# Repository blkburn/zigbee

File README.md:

# Zigbee

This repository contains multiple projects relating to teh Zigbee wireless protocol.

- zed_sensor_cc2652
- hardware
- sensor controller
- zigbee2mqtt

---

## zed_sensor_cc2652

This is a Zigbee End Device based on the Texas Instruments CC2652R1. It supports the following sensors (with build switches):
- AHT10 Temperature and Humidity Sensor
- APDS9930 Digital Proximity and Ambient Light Sensor
- LTR390 UV Light Sensor
- PIR Movement Sensor
- Reed Switch (Door opening sensor)
- Mains Energy Monitor (split coil current transformer)

The Sensor Controller handles all the sensor communications, while the main process handles the Zigbee stack and a custom task to process sensor reading and notify the Zigbee stack.

Tested with Zigbee2MQTT version 1.22.1 commit: 89996835

Master branch is currently built with:
* CCStudio version: 11.1.0.00011 
* SDK: simplelink_cc13x2_26x2_sdk_5_20_00_52

update of https://github.com/blkburn/cc2652_zigbee_zed

---

## Hardware

KiCad schematic and PCB designs. Both boards have be manufactured, tested, and working.

### Zigbee End Device
Based on the CC2652R module from RF Star (RF-BM-2652B1).
This is version 2 of the Zigbee End Device design in https://github.com/blkburn/cc2652_zigbee_zed/tree/master/hardware/cc2652_rf_star, and supports all the sensors described above. The version 1 board working unmodified with the zed_sensor_cc2652 software.

### Zigbee Coordinator
Based on the CC2652P module from RF Star (RF-BM-2652P2). It is a daughter board for the Orange Pi Zero 2 (http://www.orangepi.org/Orange%20Pi%20Zero2/). The Orange Pi uses an Allwinner H616 processor and comfortably runs Ubuntu or Debian Linux (plus much cheaper than a Raspberry Pi 4).

---

## Sensor Controller

This contains all the sensor controller projects that are used in the Zigbee End Device.

## Zigbee2MQTT

This directory contains the custom javascript device file for zigbee2mqtt to recognize the sensors.

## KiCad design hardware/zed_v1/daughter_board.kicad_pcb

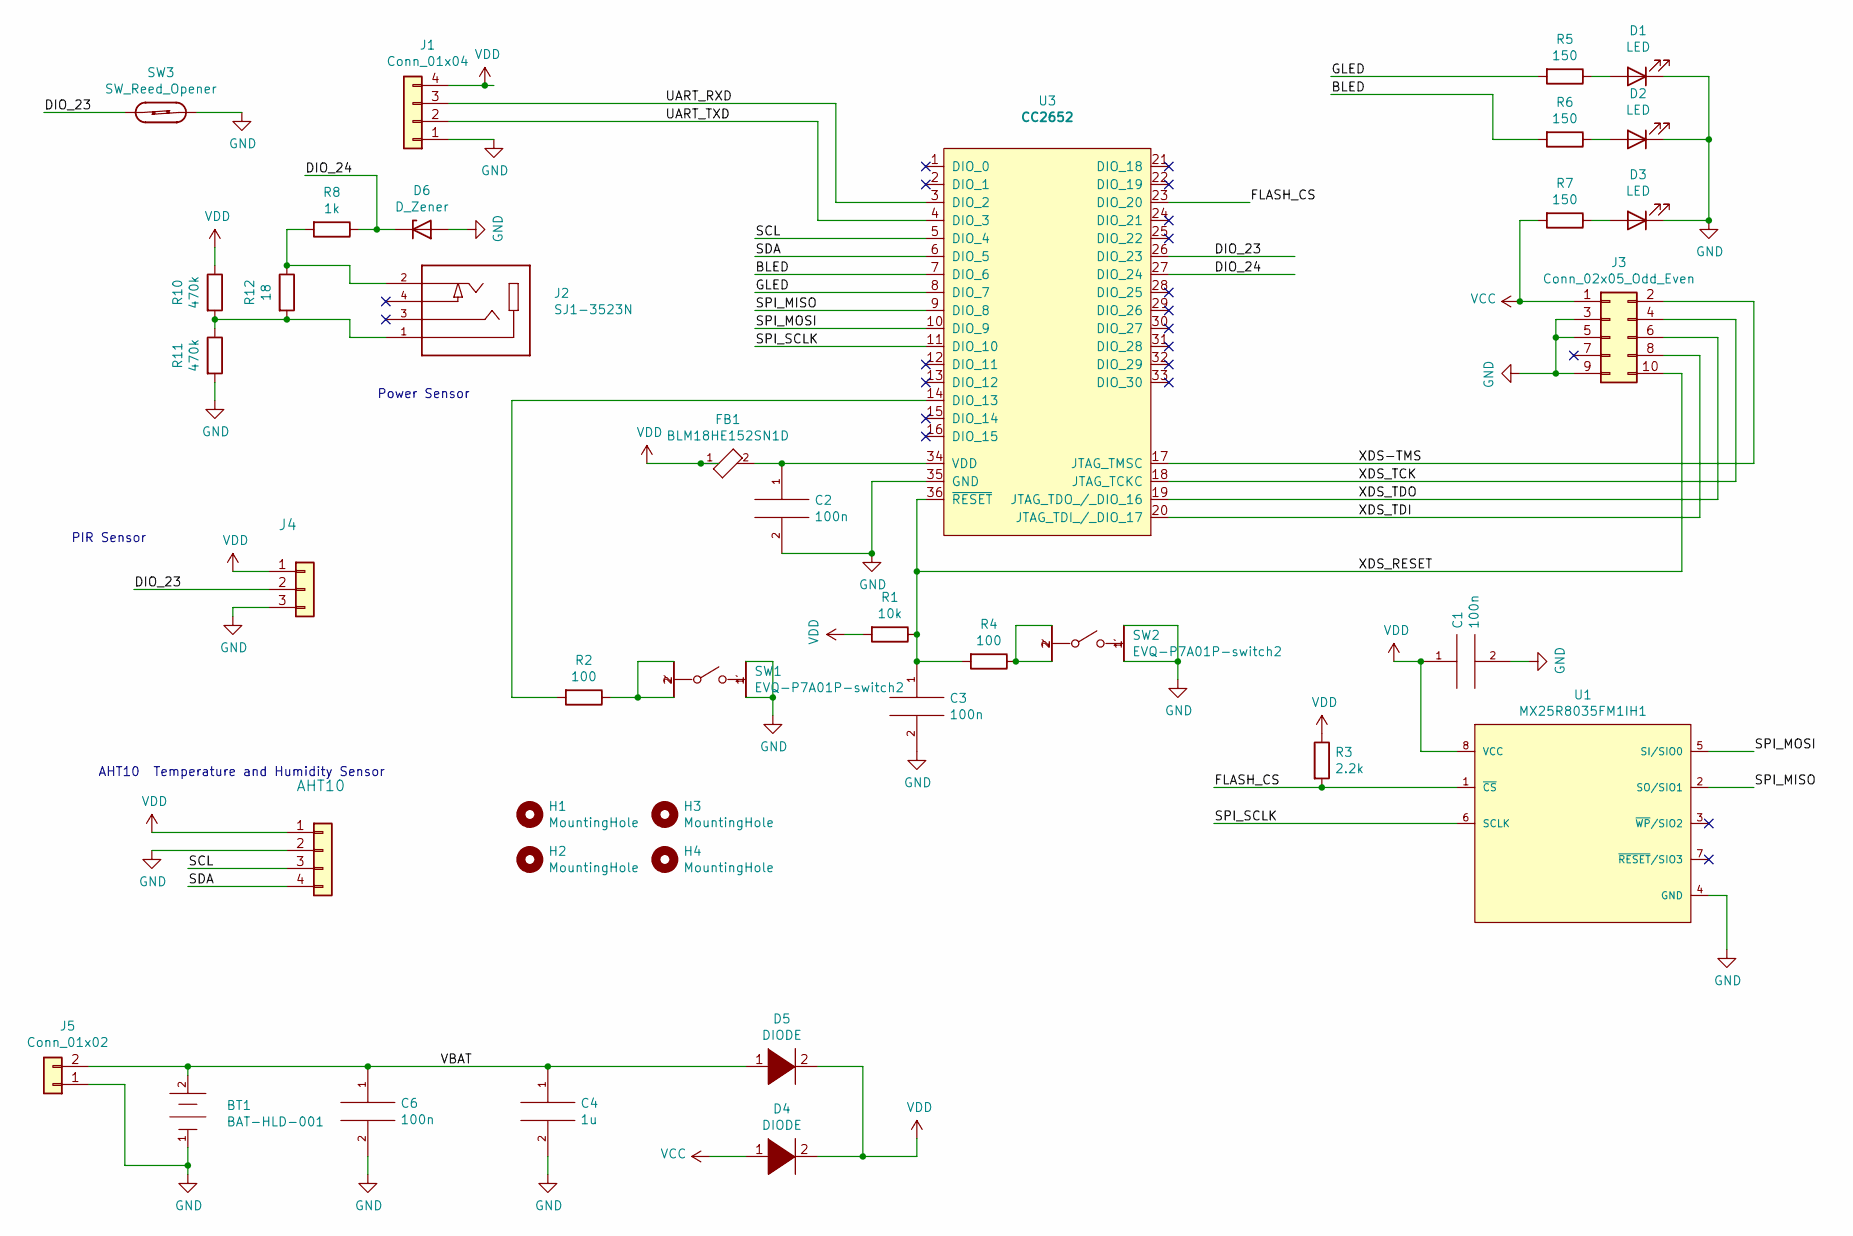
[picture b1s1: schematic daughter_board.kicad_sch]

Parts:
AHT10: Conn_01x04; PinHeader_1x04_P2.54mm_Vertical
BT1: BAT-HLD-001; Linx-BAT-HLD-001-0; mouser part number 712-BAT-HLD-001; digikey description HOLDER BATTERY 20MM COIN
C1, C2, C3, C6: 100n; C_0805_2012Metric
C4: 1u; C_0805_2012Metric
D1, D2, D3: LED; Lite-On-LTST-S220KRKT-0-0-0
D4, D5: DIODE; SOD-123FL
D6: D_Zener; D_SOD-923
FB1: BLM18HE152SN1D; R_0603_1608Metric_Pad0.98x0.95mm_HandSolder; tolerance 25%
H1, H2, H3, H4: MountingHole; MountingHole_2.7mm_M2.5_DIN965_Pad
J1: Conn_01x04; PinHeader_1x04_P2.54mm_Vertical
J2: SJ1-3523N; CUI_SJ-3524-SMT; PARTREV 1.02
J3: Conn_02x05_Odd_Even; PinHeader_2x05_P1.27mm_Vertical
J4: Conn_01x03; PinHeader_1x03_P2.54mm_Vertical
J5: Conn_01x02; JST_PH_B2B-PH-K_1x02_P2.00mm_Vertical
R1: 10k; R_0805_2012Metric
R2, R4: 100; R_0805_2012Metric
R3: 2.2k; R_0805_2012Metric
R5, R6, R7: 150; R_0805_2012Metric
R8: 1k; R_0805_2012Metric
R10, R11: 470k; R_0805_2012Metric
R12: 18; RESC1633X60N
SW1, SW2: EVQ-P7A01P-switch2; Panasonic-EVQ-P7A01P-0-0-MFG; voltage rating DC 12V; mouser part number 667-EVQP7A01P; digikey description SWITCH TACTILE SPST-NO 0.05A 12V
SW3: SW_Reed_Opener; R_Axial_DIN0309_L9.0mm_D3.2mm_P20.32mm_Horizontal
U1: MX25R8035FM1IH1; SOP-8_3.9x4.9mm_P1.27mm; digikey description IC FLASH 8M SPI 33MHZ 8USON
U3: CC2652; rf_star_cc2652

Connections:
/BLED: R6.2, U3.7 (DIO_6)
/DIO_23: J4.2, SW3.1, U3.26 (DIO_23)
/DIO_24: D6.1 (K), R8.1, U3.27 (DIO_24)
/FLASH_CS: R3.2, U1.1 (~CS), U3.23 (DIO_20)
/GLED: R5.2, U3.8 (DIO_7)
/SCL: AHT10.3, U3.5 (DIO_4)
/SDA: AHT10.4, U3.6 (DIO_5)
/SPI_MISO: U1.2 (SO/SIO1), U3.9 (DIO_8)
/SPI_MOSI: U1.5 (SI/SIO0), U3.10 (DIO_9)
/SPI_SCLK: U1.6 (SCLK), U3.11 (DIO_10)
/UART_RXD: J1.3, U3.3 (DIO_2)
/UART_TXD: J1.2, U3.4 (DIO_3)
/VBAT: BT1.2 (ANODE), C4.1, C6.1, D5.1 (K), J5.2
/XDS-TMS: J3.2, U3.17 (JTAG_TMSC)
/XDS_RESET: C3.1, J3.10, R1.1, R4.2, U3.36 (~RESET)
/XDS_TCK: J3.4, U3.18 (JTAG_TCKC)
/XDS_TDI: J3.8, U3.20 (JTAG_TDI_/_DIO_17)
/XDS_TDO: J3.6, U3.19 (JTAG_TDO_/_DIO_16)
GND: AHT10.2, BT1.1 (CATHODE), C1.2, C2.2, C3.2, C4.2, C6.2, D1.1 (K), D2.1 (K), D3.1 (K), D6.2 (A), J1.1, J3.3, J3.5, J3.9, J4.3, J5.1, R11.2, SW1.1, SW1.1', SW2.1, SW2.1', SW3.2, U1.4 (GND), U3.35 (GND)
unnamed: C2.1, FB1.2, U3.34 (VDD)
unnamed: D1.2 (A), R5.1
unnamed: D2.2 (A), R6.1
unnamed: D3.2 (A), R7.1
unnamed: J2.1, R10.2, R11.1, R12.2
unnamed: J2.2, R8.2, R12.1
unnamed: R2.1, SW1.2, SW1.2'
unnamed: R2.2, U3.14 (DIO_13)
unnamed: R4.1, SW2.2, SW2.2'
VCC: D4.1 (K), J3.1, R7.2
VDD: AHT10.1, C1.1, D4.2 (A), D5.2 (A), FB1.1, J1.4, J4.1, R1.2, R3.1, R10.1, U1.8 (VCC)

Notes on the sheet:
PIR Sensor
AHT10 Temperature and Humidity Sensor
Power Sensor

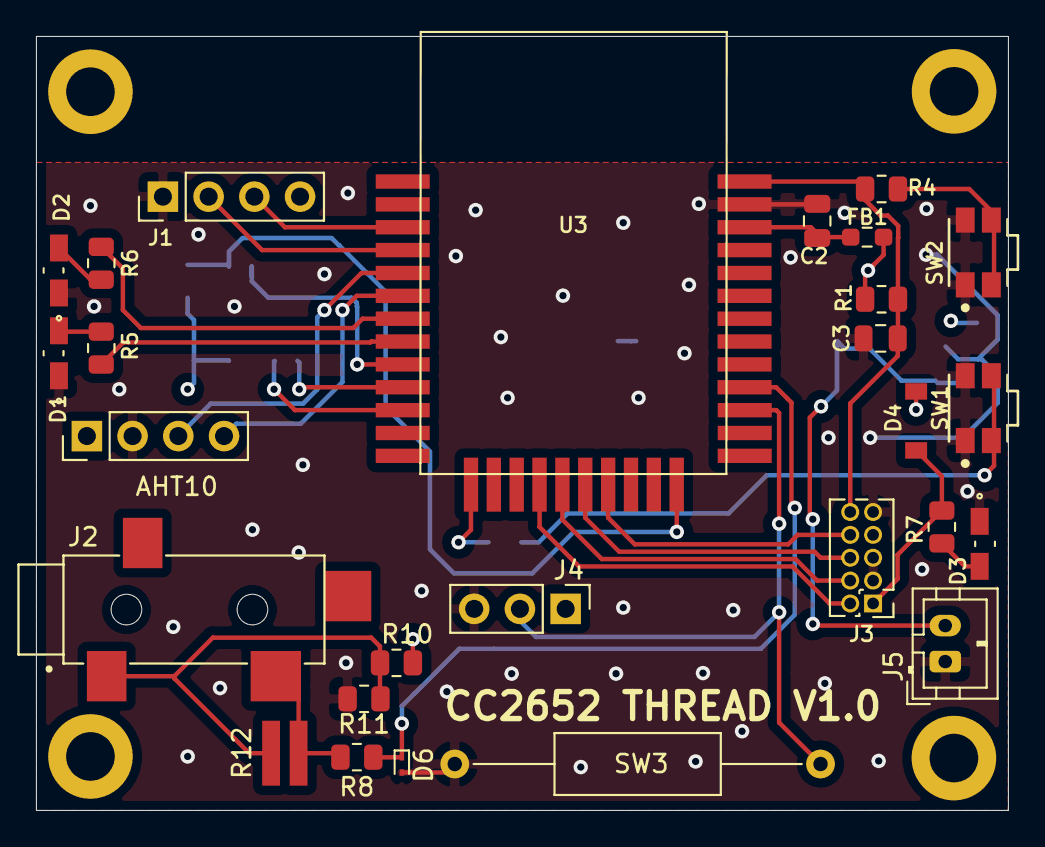
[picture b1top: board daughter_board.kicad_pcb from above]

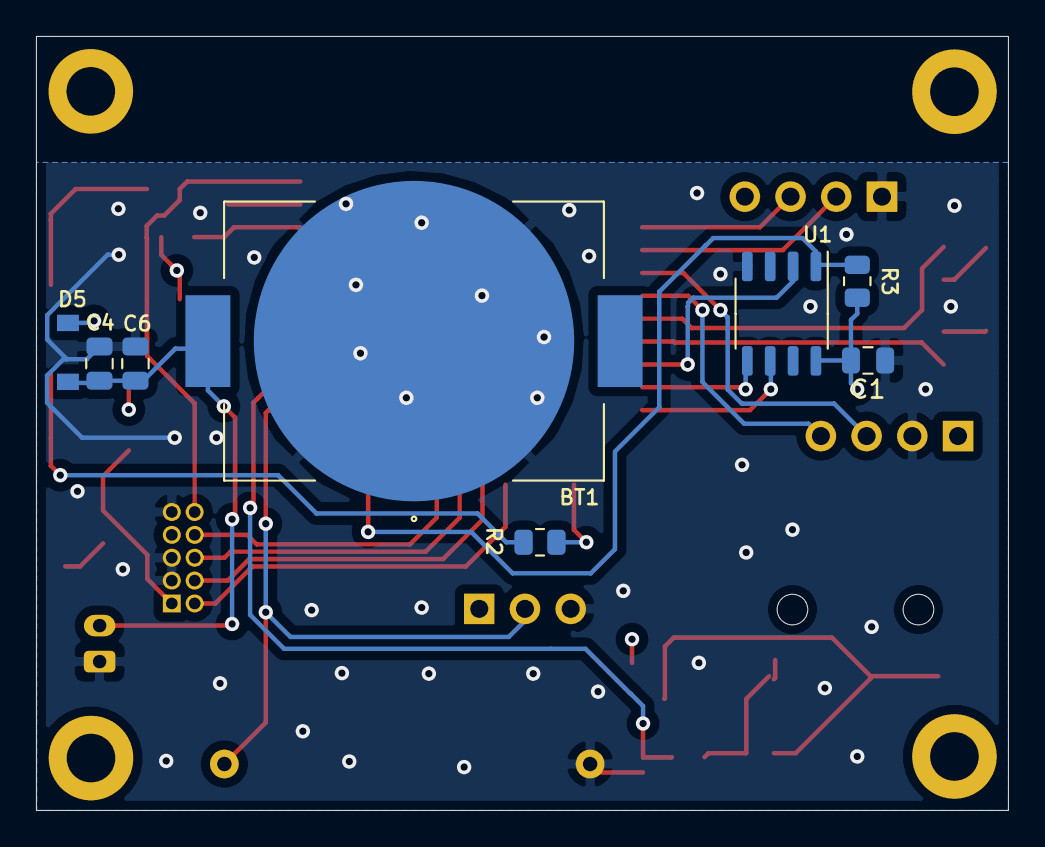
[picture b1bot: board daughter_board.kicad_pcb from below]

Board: 4 copper layers, 54.0 x 43.0 mm, 39 parts (8 on the bottom side), 30 nets.

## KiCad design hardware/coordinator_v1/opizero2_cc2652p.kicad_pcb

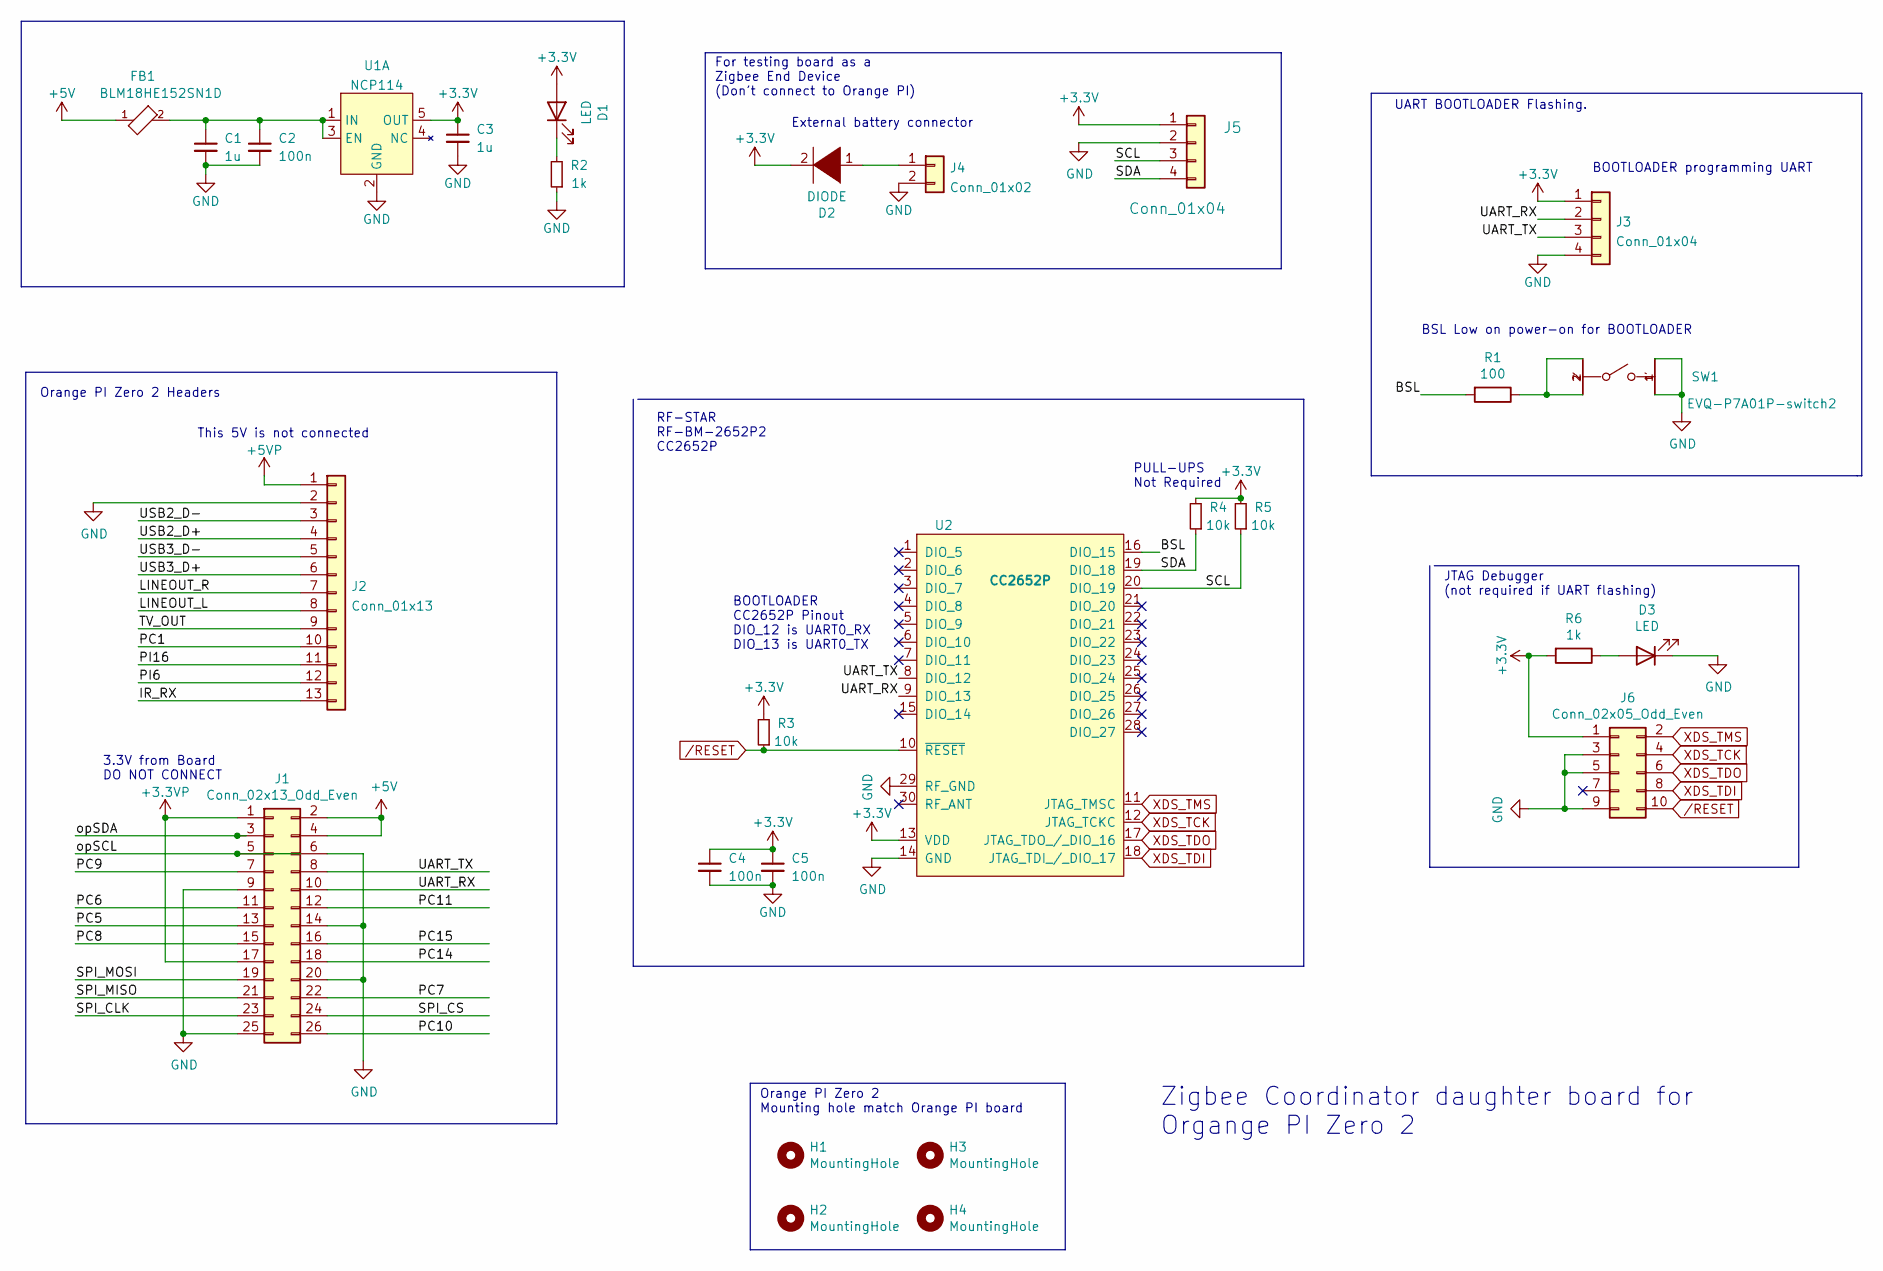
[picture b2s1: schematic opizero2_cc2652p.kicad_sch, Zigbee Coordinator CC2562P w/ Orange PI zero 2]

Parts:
C1, C3: 1u; C_1206_3216Metric; LCSC Part # C13585
C2, C4, C5: 100n; C_0805_2012Metric; LCSC Part # C13585
D1, D3: LED; Lite-On-LTST-S220KRKT-0-0-0
D2: DIODE; SOD-123FL
FB1: BLM18HE152SN1D; R_0603_1608Metric_Pad0.98x0.95mm_HandSolder; tolerance 25%
H1, H2, H3, H4: MountingHole; MountingHole_2.7mm_M2.5_ISO14580_Pad
J1: Conn_02x13_Odd_Even; PinHeader_2x13_P2.54mm_Vertical
J2: Conn_01x13; PinHeader_1x13_P2.54mm_Vertical
J3, J5: Conn_01x04; PinHeader_1x04_P2.54mm_Vertical
J4: Conn_01x02; PinHeader_1x02_P2.54mm_Vertical
J6: Conn_02x05_Odd_Even; PinHeader_2x05_P1.27mm_Vertical
R1: 100; R_0805_2012Metric
R2: 1k; R_0805_2012Metric; LCSC Part # C21190
R3, R4, R5: 10k; R_0805_2012Metric; LCSC Part # C21190
R6: 1k; R_0805_2012Metric
SW1: EVQ-P7A01P-switch2; Panasonic-EVQ-P7A01P-0-0-MFG; voltage rating DC 12V; mouser part number 667-EVQP7A01P; digikey description SWITCH TACTILE SPST-NO 0.05A 12V
U1: NCP114; TSOT-23-5
U2: CC2652P; cc2652p_rf_star

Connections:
+3.3VP: J1.1, J1.17
+3V3: C3.1, C4.1, C5.1, D1.2 (A), D2.2 (A), J3.1, J5.1, J6.1, R3.2, R4.2, R5.2, R6.2, U1.5 (OUT), U2.13 (VDD)
+5V: FB1.1, J1.2, J1.4
+5VP: J2.1
/BSL: R1.2, U2.16 (DIO_15)
/IR_RX: J2.13
/LINEOUT_L: J2.8
/LINEOUT_R: J2.7
/PC1: J2.10
/PC5: J1.13
/PC6: J1.11
/PC7: J1.22
/PC8: J1.15
/PC9: J1.7
/PC10: J1.26
/PC11: J1.12
/PC14: J1.18
/PC15: J1.16
/PI6: J2.12
/PI16: J2.11
/SCL: J5.3, R5.1, U2.20 (DIO_19)
/SDA: J5.4, R4.1, U2.19 (DIO_18)
/SPI_CLK: J1.23
/SPI_CS: J1.24
/SPI_MISO: J1.21
/SPI_MOSI: J1.19
/TV_OUT: J2.9
/UART_RX: J1.10, J3.2, U2.9 (DIO_13)
/UART_TX: J1.8, J3.3, U2.8 (DIO_12)
/USB2_D+: J2.4
/USB2_D-: J2.3
/USB3_D+: J2.6
/USB3_D-: J2.5
/opSCL: J1.5
/opSDA: J1.3
GND: C1.2, C2.2, C3.2, C4.2, C5.2, D3.1 (K), J1.6, J1.9, J1.14, J1.20, J1.25, J2.2, J3.4, J4.2, J5.2, J6.3, J6.5, J6.9, R2.1, SW1.1, SW1.1', U1.2 (GND), U2.14 (GND), U2.29 (RF_GND)
unnamed: C1.1, C2.1, FB1.2, U1.1 (IN), U1.3 (EN)
unnamed: D1.1 (K), R2.2
unnamed: D2.1 (K), J4.1
unnamed: D3.2 (A), R6.1
unnamed: R1.1, SW1.2, SW1.2'
XDS_TCK: J6.4, U2.12 (JTAG_TCKC)
XDS_TDI: J6.8, U2.18 (JTAG_TDI_/_DIO_17)
XDS_TDO: J6.6, U2.17 (JTAG_TDO_/_DIO_16)
XDS_TMS: J6.2, U2.11 (JTAG_TMSC)
/RESET: J6.10, R3.1, U2.10 (~RESET)

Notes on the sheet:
Zigbee Coordinator daughter board for Organge PI Zero 2
BOOTLOADER CC2652P Pinout DIO_12 is UART0_RX DIO_13 is UART0_TX
Orange PI Zero 2 Headers
For testing board as a Zigbee End Device (Don't connect to Orange PI)
UART BOOTLOADER Flashing.
3.3V from Board DO NOT CONNECT
JTAG Debugger (not required if UART flashing)
BOOTLOADER programming UART
RF-STAR RF-BM-2652P2 CC2652P
External battery connector
Orange PI Zero 2 Mounting hole match Orange PI board
This 5V is not connected
PULL-UPS Not Required
BSL Low on power-on for BOOTLOADER

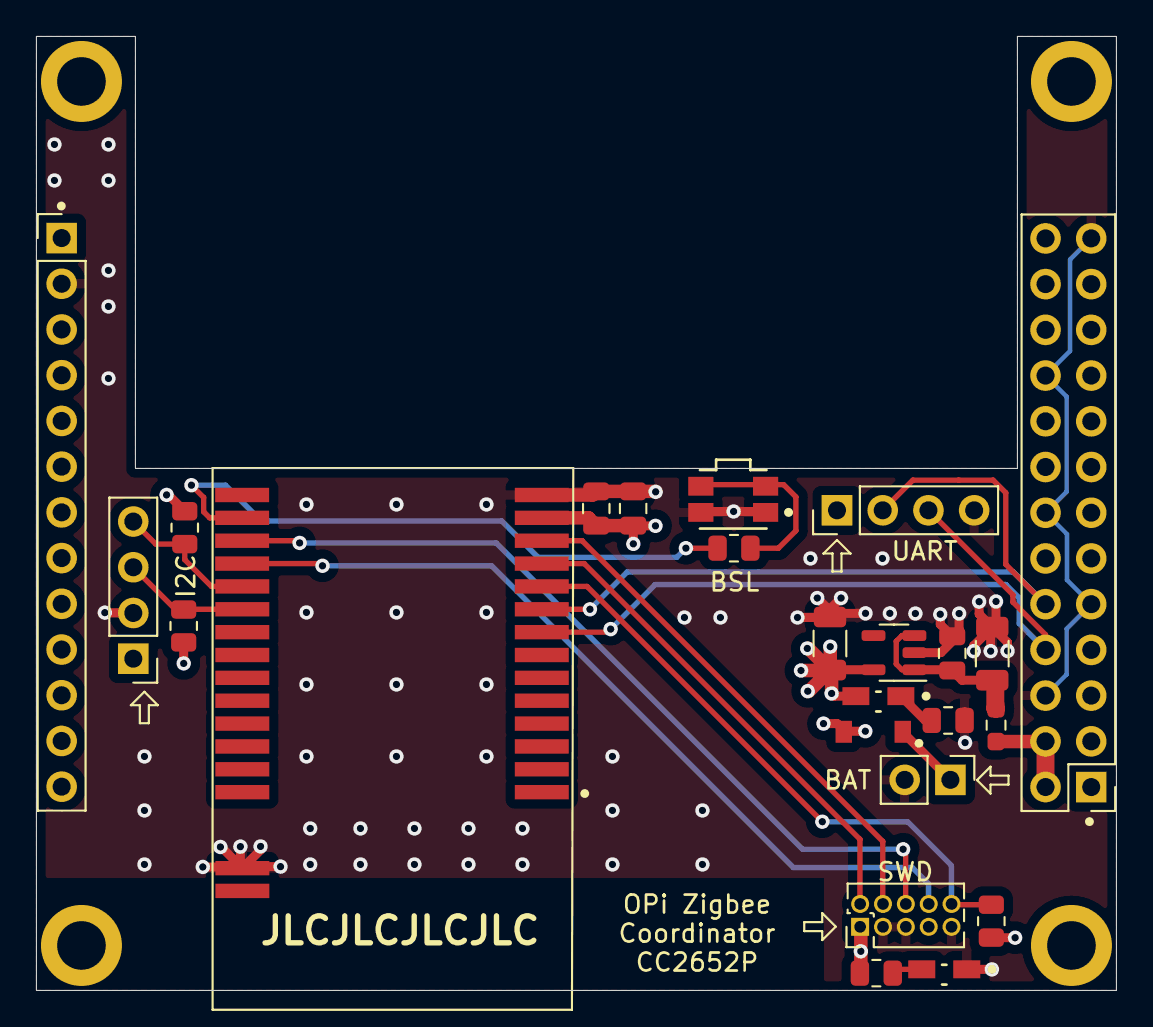
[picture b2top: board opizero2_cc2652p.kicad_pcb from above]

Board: 4 copper layers, 60.0 x 53.0 mm, 28 parts (0 on the bottom side), 19 nets.

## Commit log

2022-02-08 add new zigbee repo
2022-02-08 add sensor controller source
2022-02-08 zigbee2mqtt external converter
2022-02-10 added hardware files
